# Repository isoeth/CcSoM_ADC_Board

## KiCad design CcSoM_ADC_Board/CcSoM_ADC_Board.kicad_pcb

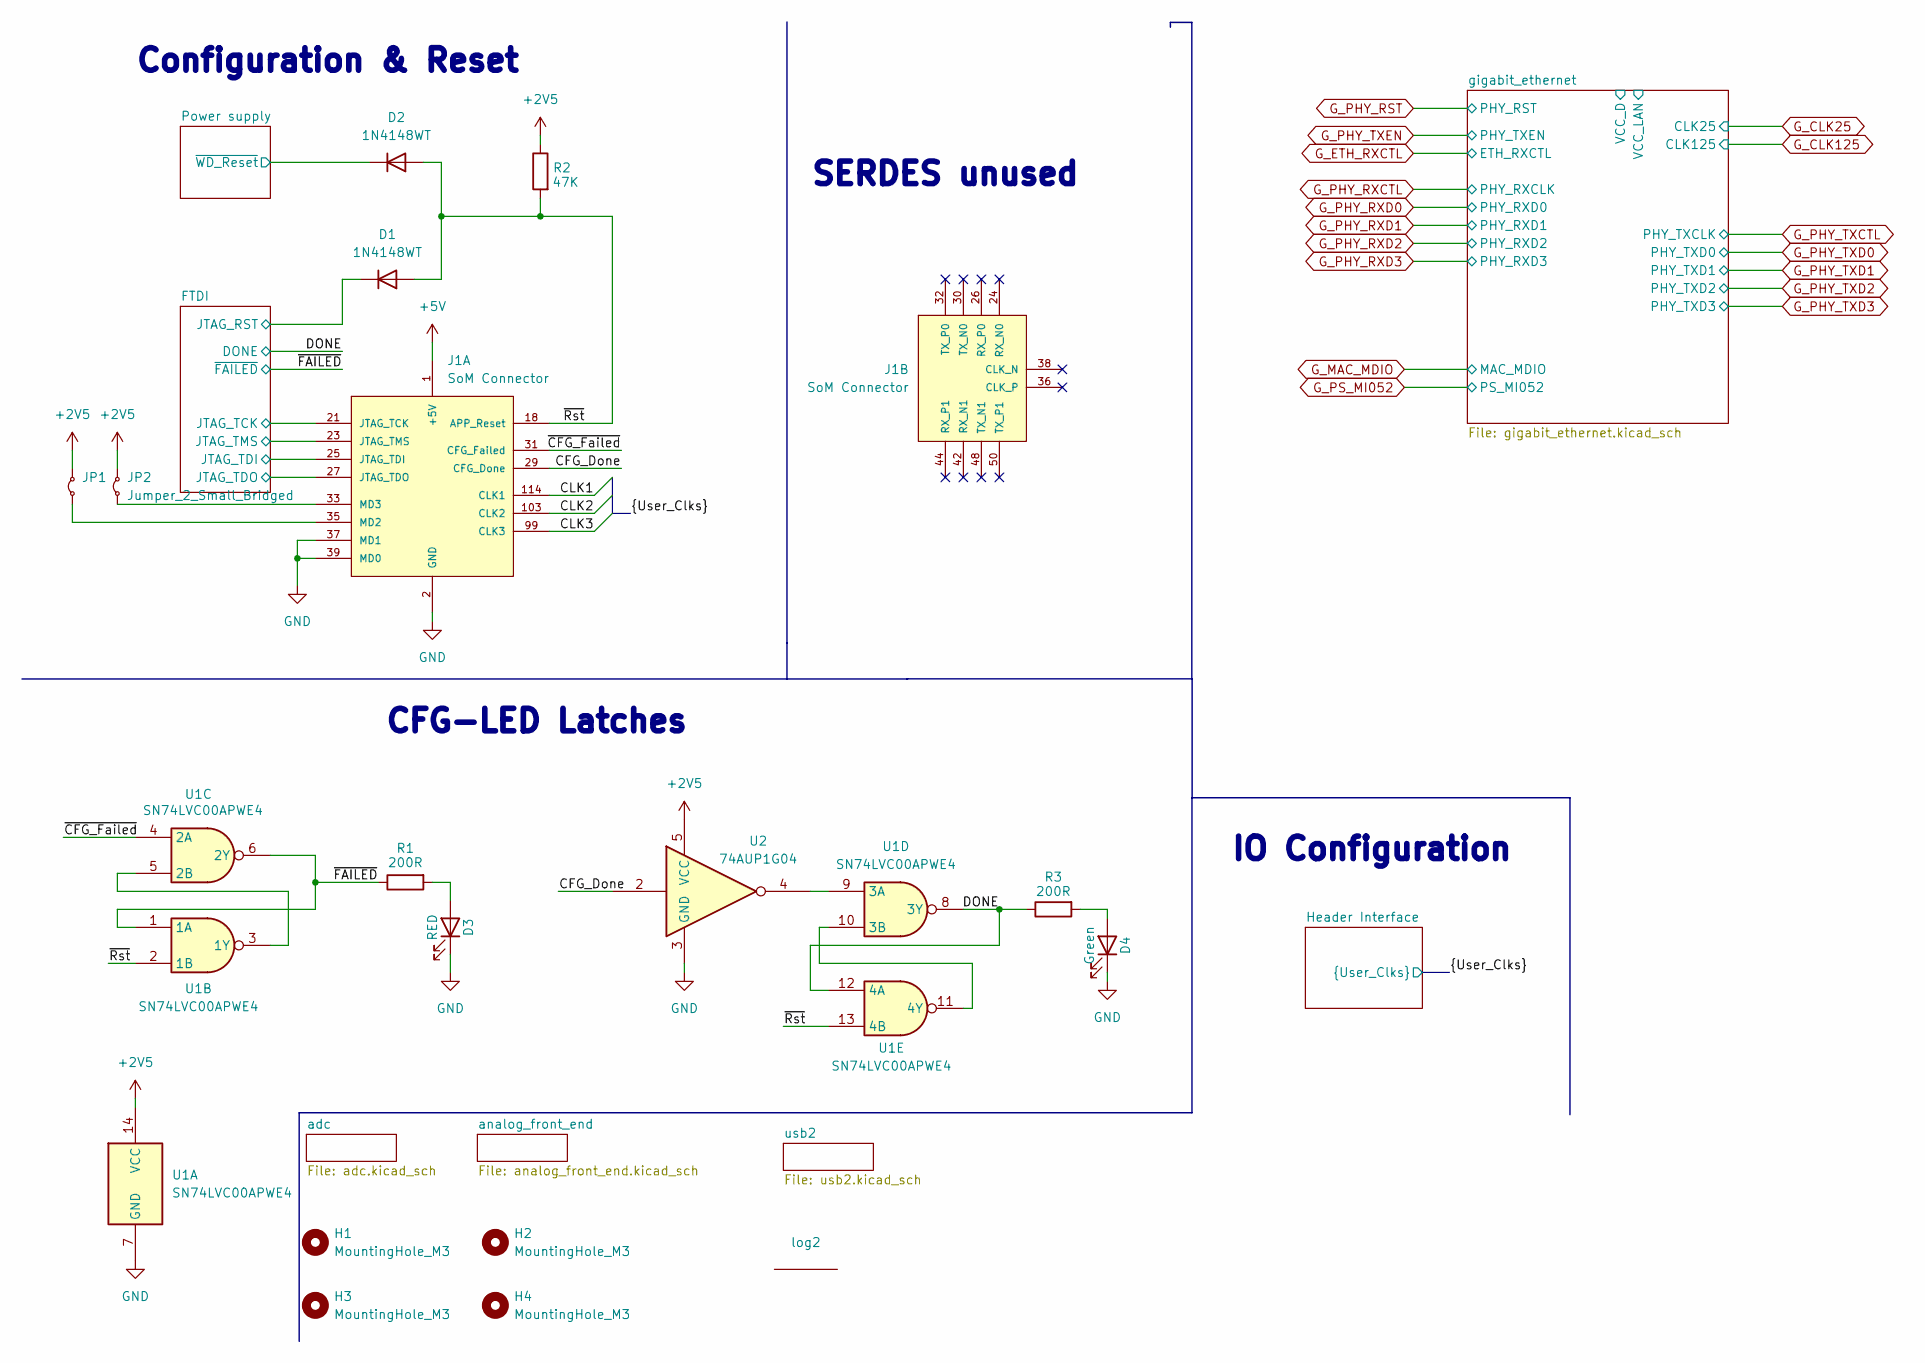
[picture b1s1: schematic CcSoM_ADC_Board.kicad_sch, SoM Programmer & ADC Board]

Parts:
D1, D2: 1N4148WT; LED_0603_1608Metric; Mouser Part Number 637-1N4148WT
D3: RED; LED_0603_1608Metric; Mouser Part Number 710-150060SS75000
D4: Green; LED_0603_1608Metric; Mouser Part Number 710-150060VS75000
H1, H2, H3, H4: MountingHole_M3; MountingHole_3.2mm_M3
J1: SoM Connector; SoM_Connector; Mouser Part Number 571-1-1473005-1
JP1, JP2: Jumper_2_Small_Bridged; TestPoint_2Pads_Pitch2.54mm_Drill0.8mm; DigiKey_no 664-G800W306018EU-ND
R1, R3: 200R; R_0603_1608Metric; Mouser Part Number 71-CRCW0603200RFKEC
R2: 47K; R_0603_1608Metric; Mouser Part Number 71-CRCW060347K0FKED
U1: SN74LVC00APWE4; TSSOP-14_4.4x5mm_P0.65mm; Mouser Part Number 595-SN74LVC00APWE4
U2: 74AUP1G04; SOT-23-5; Mouser Part Number 595-SN74AUP1G04DBVR
log2: OpenHardwareLogo

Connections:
+5V: J1.1 (+5V), J1.4 (+5V); also elsewhere on the board
/CFG_Done: J1.29 (CFG_Done), U2.2
/CLK1: J1.114 (CLK1)
/CLK2: J1.103 (CLK2)
/CLK3: J1.99 (CLK3)
/DONE: R3.1, U1.8 (3Y), U1.12 (4A); also elsewhere on the board
/FTDI/JTAG_RST: D1.1 (K); also elsewhere on the board
/FTDI/JTAG_TCK: J1.21 (JTAG_TCK); also elsewhere on the board
/FTDI/JTAG_TDI: J1.25 (JTAG_TDI); also elsewhere on the board
/FTDI/JTAG_TDO: J1.27 (JTAG_TDO); also elsewhere on the board
/FTDI/JTAG_TMS: J1.23 (JTAG_TMS); also elsewhere on the board
/Power supply/~WD_Reset: D2.1 (K); also elsewhere on the board
/~CFG_Failed: J1.31 (CFG_Failed), U1.4 (2A)
/~FAILED: R1.1, U1.1 (1A), U1.6 (2Y); also elsewhere on the board
/~Rst: D1.2 (A), D2.2 (A), J1.18 (APP_Reset), R2.2, U1.2 (1B), U1.13 (4B)
unnamed: D3.2 (A), R1.2
unnamed: D4.2 (A), R3.2
unnamed: J1.35 (MD2), JP1.2 (B)
unnamed: J1.33 (MD3), JP2.2 (B)
unnamed: U1.3 (1Y), U1.5 (2B)
unnamed: U1.9 (3A), U2.4
unnamed: U1.10 (3B), U1.11 (4Y)
OGND: D3.1 (K), D4.1 (K), J1.2 (GND), J1.3 (GND), J1.6 (GND), J1.7 (GND), J1.10 (GND), J1.11 (GND), J1.14 (GND), J1.15 (GND), J1.19 (GND), J1.20 (GND), J1.22 (GND), J1.28 (GND), J1.34 (GND), J1.37 (MD1), J1.39 (MD0), J1.40 (GND), J1.46 (GND), J1.52 (GND), J1.54 (GND), J1.97 (GND), J1.101 (GND), J1.105 (GND), J1.112 (GND), J1.116 (GND), J1.122 (GND), J1.144 (GND), J1.159 (GND), J1.162 (GND), J1.180 (GND), J1.181 (GND), J1.199 (GND), J1.S1 (SHIELD), J1.S2 (SHIELD__1), U1.7 (GND), U2.3 (GND); also elsewhere on the board
OVDD: JP1.1 (A), JP2.1 (A), R2.1, U1.14 (VCC), U2.5 (VCC); also elsewhere on the board

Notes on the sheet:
Configuration & Reset
CFG-LED Latches
IO Configuration
SERDES unused

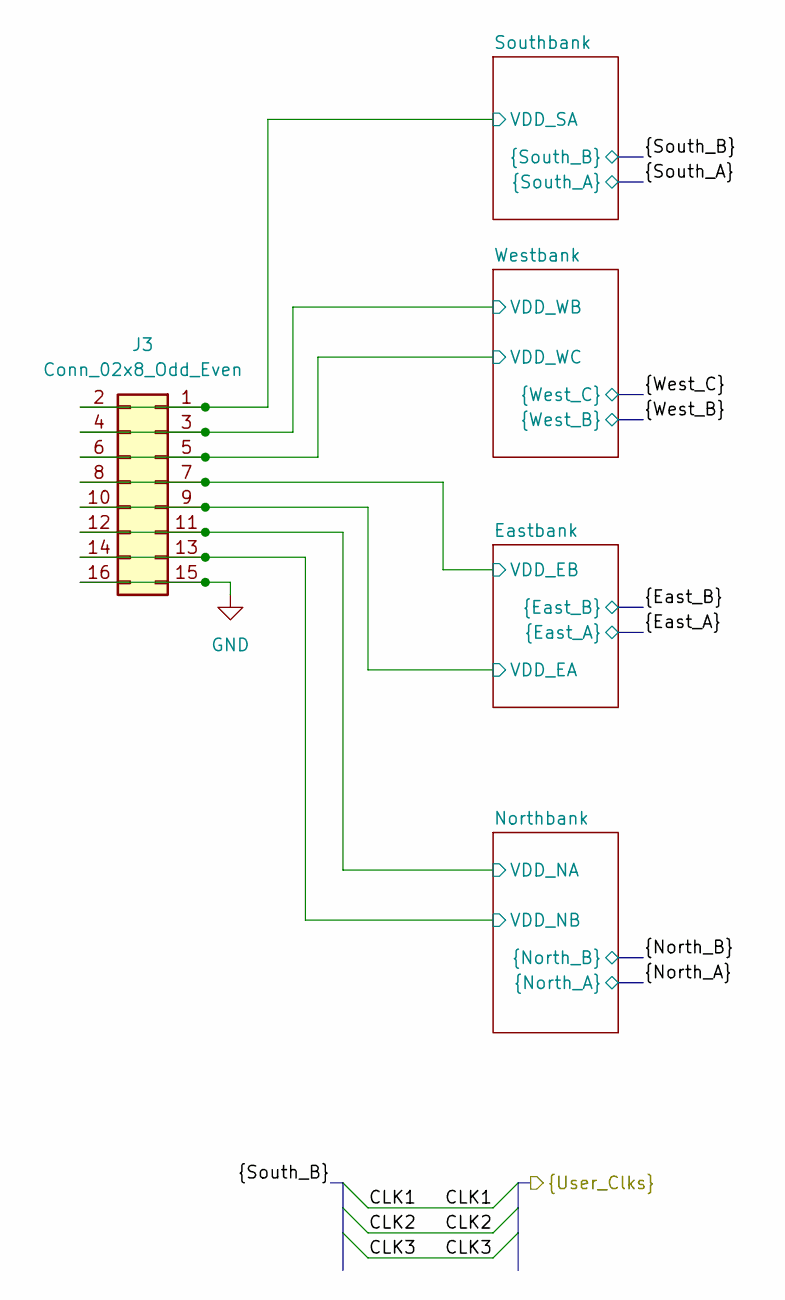
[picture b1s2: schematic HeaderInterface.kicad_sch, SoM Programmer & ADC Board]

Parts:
J3: Conn_02x8_Odd_Even; PinHeader_2x08_P2.54mm_Vertical; Mouser Part Number 649-1012938191601BLF

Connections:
/Header Interface/Eastbank/VDD_EA: J3.9, J3.10; also elsewhere on the board
/Header Interface/Eastbank/VDD_EB: J3.7, J3.8; also elsewhere on the board
/Header Interface/Northbank/VDD_NA: J3.11, J3.12; also elsewhere on the board
/Header Interface/Northbank/VDD_NB: J3.13, J3.14; also elsewhere on the board
/Header Interface/Southbank/VDD_SA: J3.1, J3.2; also elsewhere on the board
/Header Interface/Westbank/VDD_WB: J3.3, J3.4; also elsewhere on the board
/Header Interface/Westbank/VDD_WC: J3.5, J3.6; also elsewhere on the board
OGND: J3.15, J3.16; also elsewhere on the board

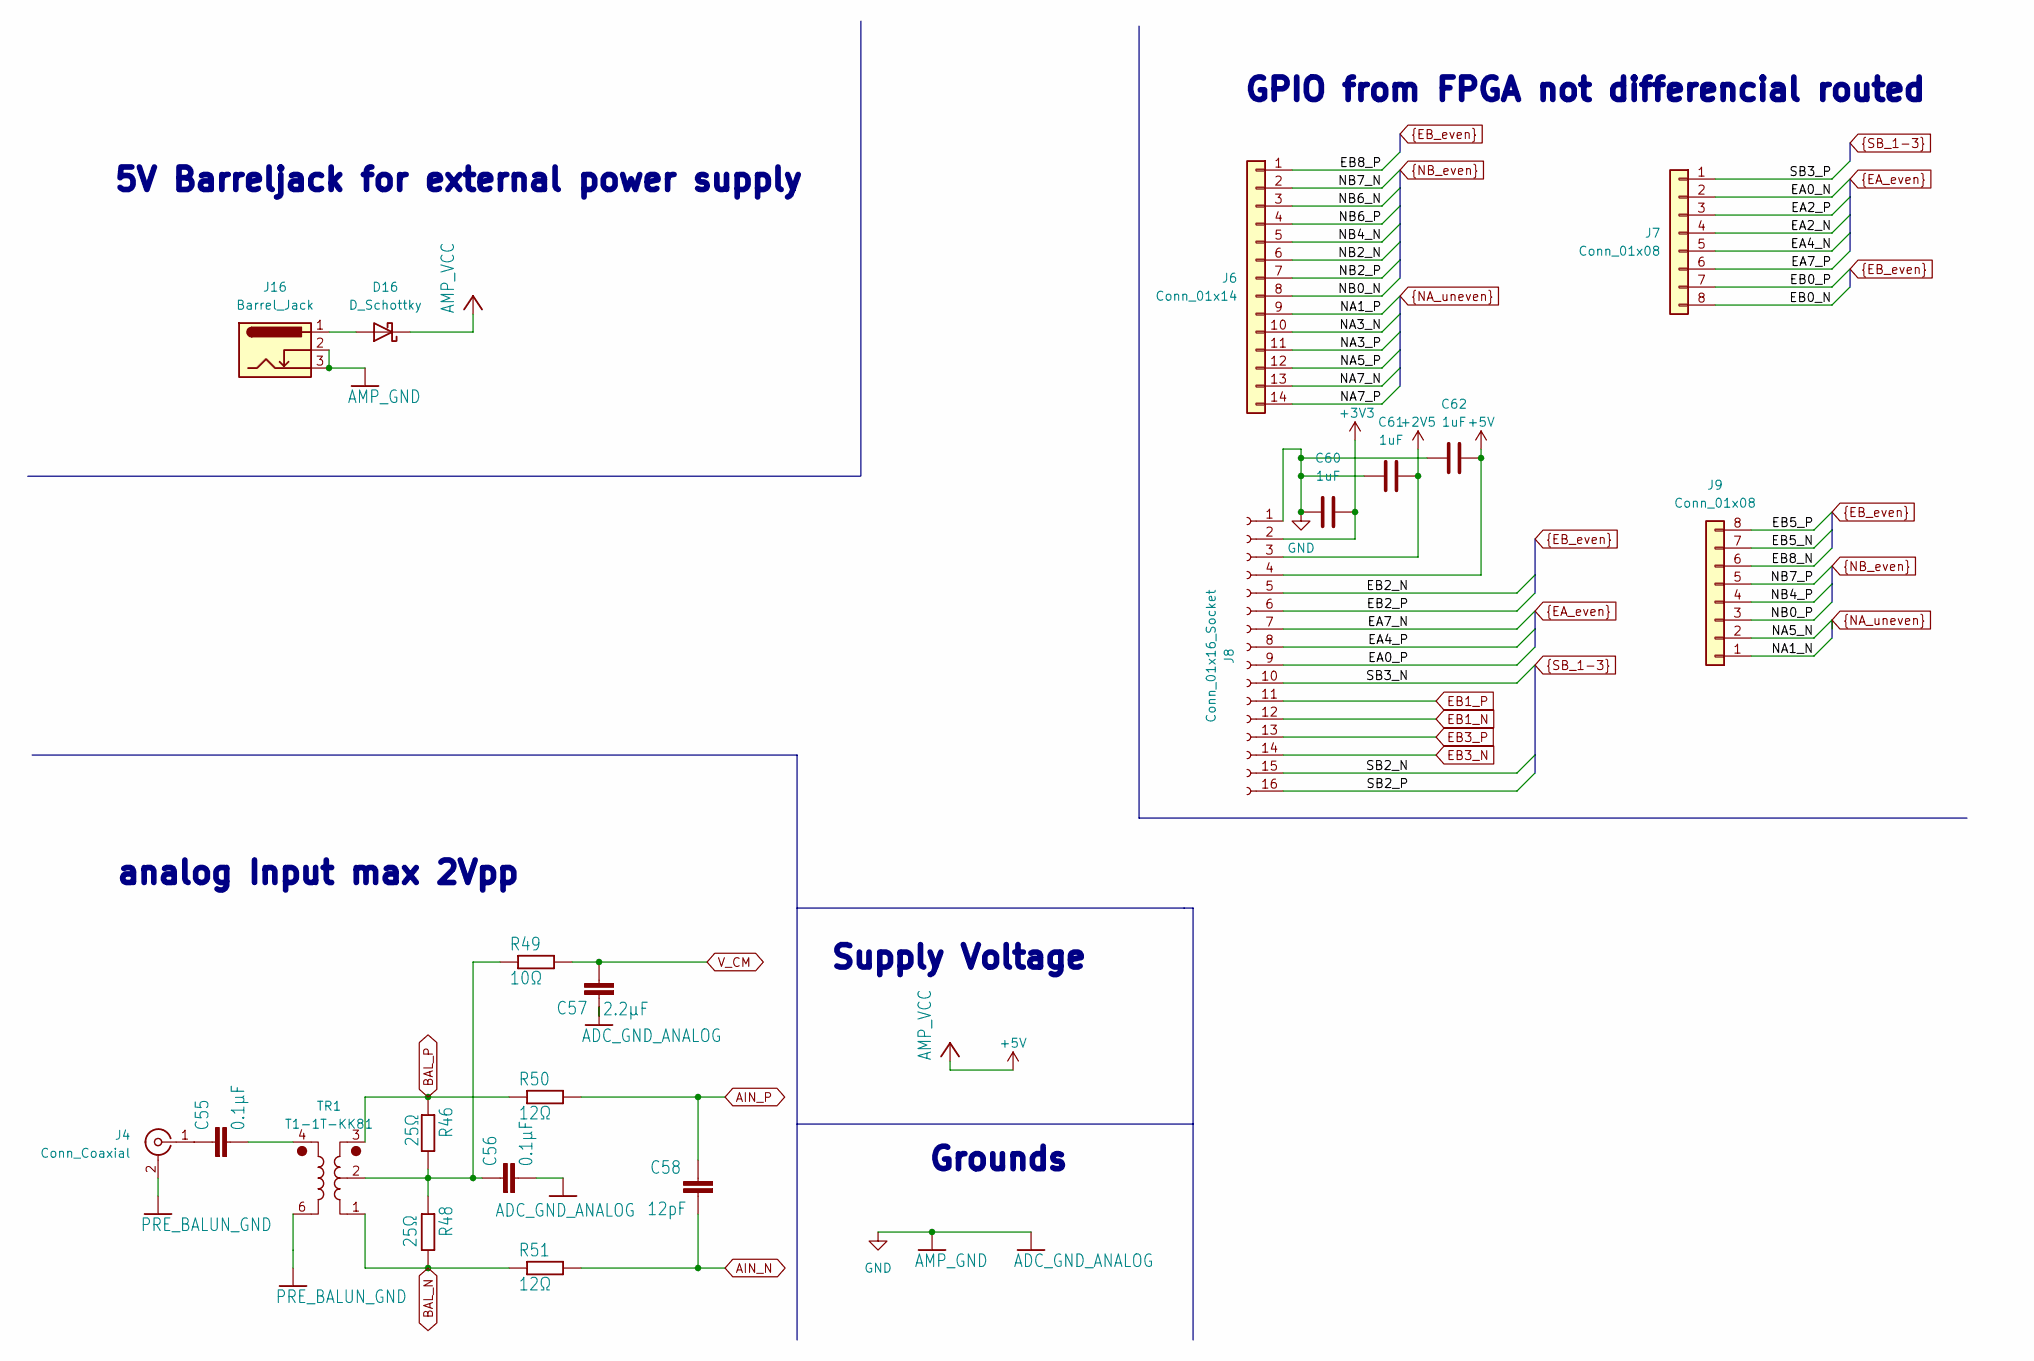
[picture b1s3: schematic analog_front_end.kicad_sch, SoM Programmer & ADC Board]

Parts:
C55, C56: 0.1μF; C_0402_1005Metric_Pad0.74x0.62mm_HandSolder; DigiKey_no C0402C104K4RACTU
C57: 2.2μF; C_0402_1005Metric_Pad0.74x0.62mm_HandSolder; DigiKey_no 490-10012-1-ND
C58: 12pF; C_0402_1005Metric_Pad0.74x0.62mm_HandSolder; DigiKey_no 399-C0402C120J5GACTUCT-ND
C60, C61, C62: 1uF; C_0603_1608Metric; Mouser Part Number 80-C0603C104M4R7411
D16: D_Schottky; D_0805_2012Metric_Pad1.15x1.40mm_HandSolder; DigiKey_no 478-7800-1-ND
J4: Conn_Coaxial; SMA_Amphenol_132134-11_Vertical; DigiKey_no ACX1995-ND
J6: Conn_01x14; PinSocket_1x14_P2.54mm_Vertical; DigiKey_no S7012-ND
J7, J9: Conn_01x08; PinSocket_1x08_P2.54mm_Vertical; DigiKey_no S7006-ND
J8: Conn_01x16_Socket; PinSocket_1x16_P2.54mm_Vertical; DigiKey_no S7014-ND
J16: Barrel_Jack; BarrelJack_CLIFF_FC681465S_SMT_Horizontal; DigiKey_no 4654-FC681465S-ND
R46, R48: 25Ω; R_0402_1005Metric_Pad0.72x0.64mm_HandSolder; DigiKey_no 478-UBR0402B250FZTR\500CT-ND
R49: 10Ω; R_0402_1005Metric_Pad0.72x0.64mm_HandSolder; DigiKey_no 541-10.0LCT-ND
R50, R51: 12Ω; R_0402_1005Metric_Pad0.72x0.64mm_HandSolder; DigiKey_no YAG2968CT-ND
TR1: T1-1T-KK81; DigiKey_no 3157-T1-1T-KK81+CT-ND

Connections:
+3V3: C60.2, J8.2; also elsewhere on the board
+5V: C62.2, D16.1 (K), J8.4; also elsewhere on the board
AIN_N: C58.1, R51.2; also elsewhere on the board
AIN_P: C58.2, R50.2; also elsewhere on the board
BAL_N: R48.2, R51.1, TR1.1
BAL_P: R46.1, R50.1, TR1.3
EA0_N: J7.2; also elsewhere on the board
EA0_P: J8.9; also elsewhere on the board
EA2_N: J7.4; also elsewhere on the board
EA2_P: J7.3; also elsewhere on the board
EA4_N: J7.5; also elsewhere on the board
EA4_P: J8.8; also elsewhere on the board
EA7_N: J8.7; also elsewhere on the board
EA7_P: J7.6; also elsewhere on the board
EB0_N: J7.8; also elsewhere on the board
EB0_P: J7.7; also elsewhere on the board
EB1_N: J8.12; also elsewhere on the board
EB1_P: J8.11; also elsewhere on the board
EB2_N: J8.5; also elsewhere on the board
EB2_P: J8.6; also elsewhere on the board
EB3_N: J8.14; also elsewhere on the board
EB3_P: J8.13; also elsewhere on the board
EB5_N: J9.7; also elsewhere on the board
EB5_P: J9.8; also elsewhere on the board
EB8_N: J9.6; also elsewhere on the board
EB8_P: J6.1; also elsewhere on the board
NA1_N: J9.1; also elsewhere on the board
NA1_P: J6.9; also elsewhere on the board
NA3_N: J6.10; also elsewhere on the board
NA3_P: J6.11; also elsewhere on the board
NA5_N: J9.2; also elsewhere on the board
NA5_P: J6.12; also elsewhere on the board
NA7_N: J6.13; also elsewhere on the board
NA7_P: J6.14; also elsewhere on the board
NB0_N: J6.8; also elsewhere on the board
NB0_P: J9.3; also elsewhere on the board
NB2_N: J6.6; also elsewhere on the board
NB2_P: J6.7; also elsewhere on the board
NB4_N: J6.5; also elsewhere on the board
NB4_P: J9.4; also elsewhere on the board
NB6_N: J6.3; also elsewhere on the board
NB6_P: J6.4; also elsewhere on the board
NB7_N: J6.2; also elsewhere on the board
NB7_P: J9.5; also elsewhere on the board
unnamed: C55.2, TR1.4
unnamed: C56.1, R46.2, R48.1, R49.1, TR1.2
unnamed: D16.2 (A), J16.1
unnamed: C55.1, J4.1 (In)
OGND: C56.2, C57.1, C60.1, C61.1, C62.1, J8.1, J16.2, J16.3; also elsewhere on the board
OVDD: C61.2, J8.3; also elsewhere on the board
PRE_BALUN_GND: J4.2 (Ext), TR1.6
SB2_N: J8.15; also elsewhere on the board
SB2_P: J8.16; also elsewhere on the board
SB3_N: J8.10; also elsewhere on the board
SB3_P: J7.1; also elsewhere on the board
V_CM: C57.2, R49.2; also elsewhere on the board

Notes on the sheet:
GPIO from FPGA not differencial routed
Supply Voltage
analog Input max 2Vpp
5V Barreljack for external power supply
Grounds

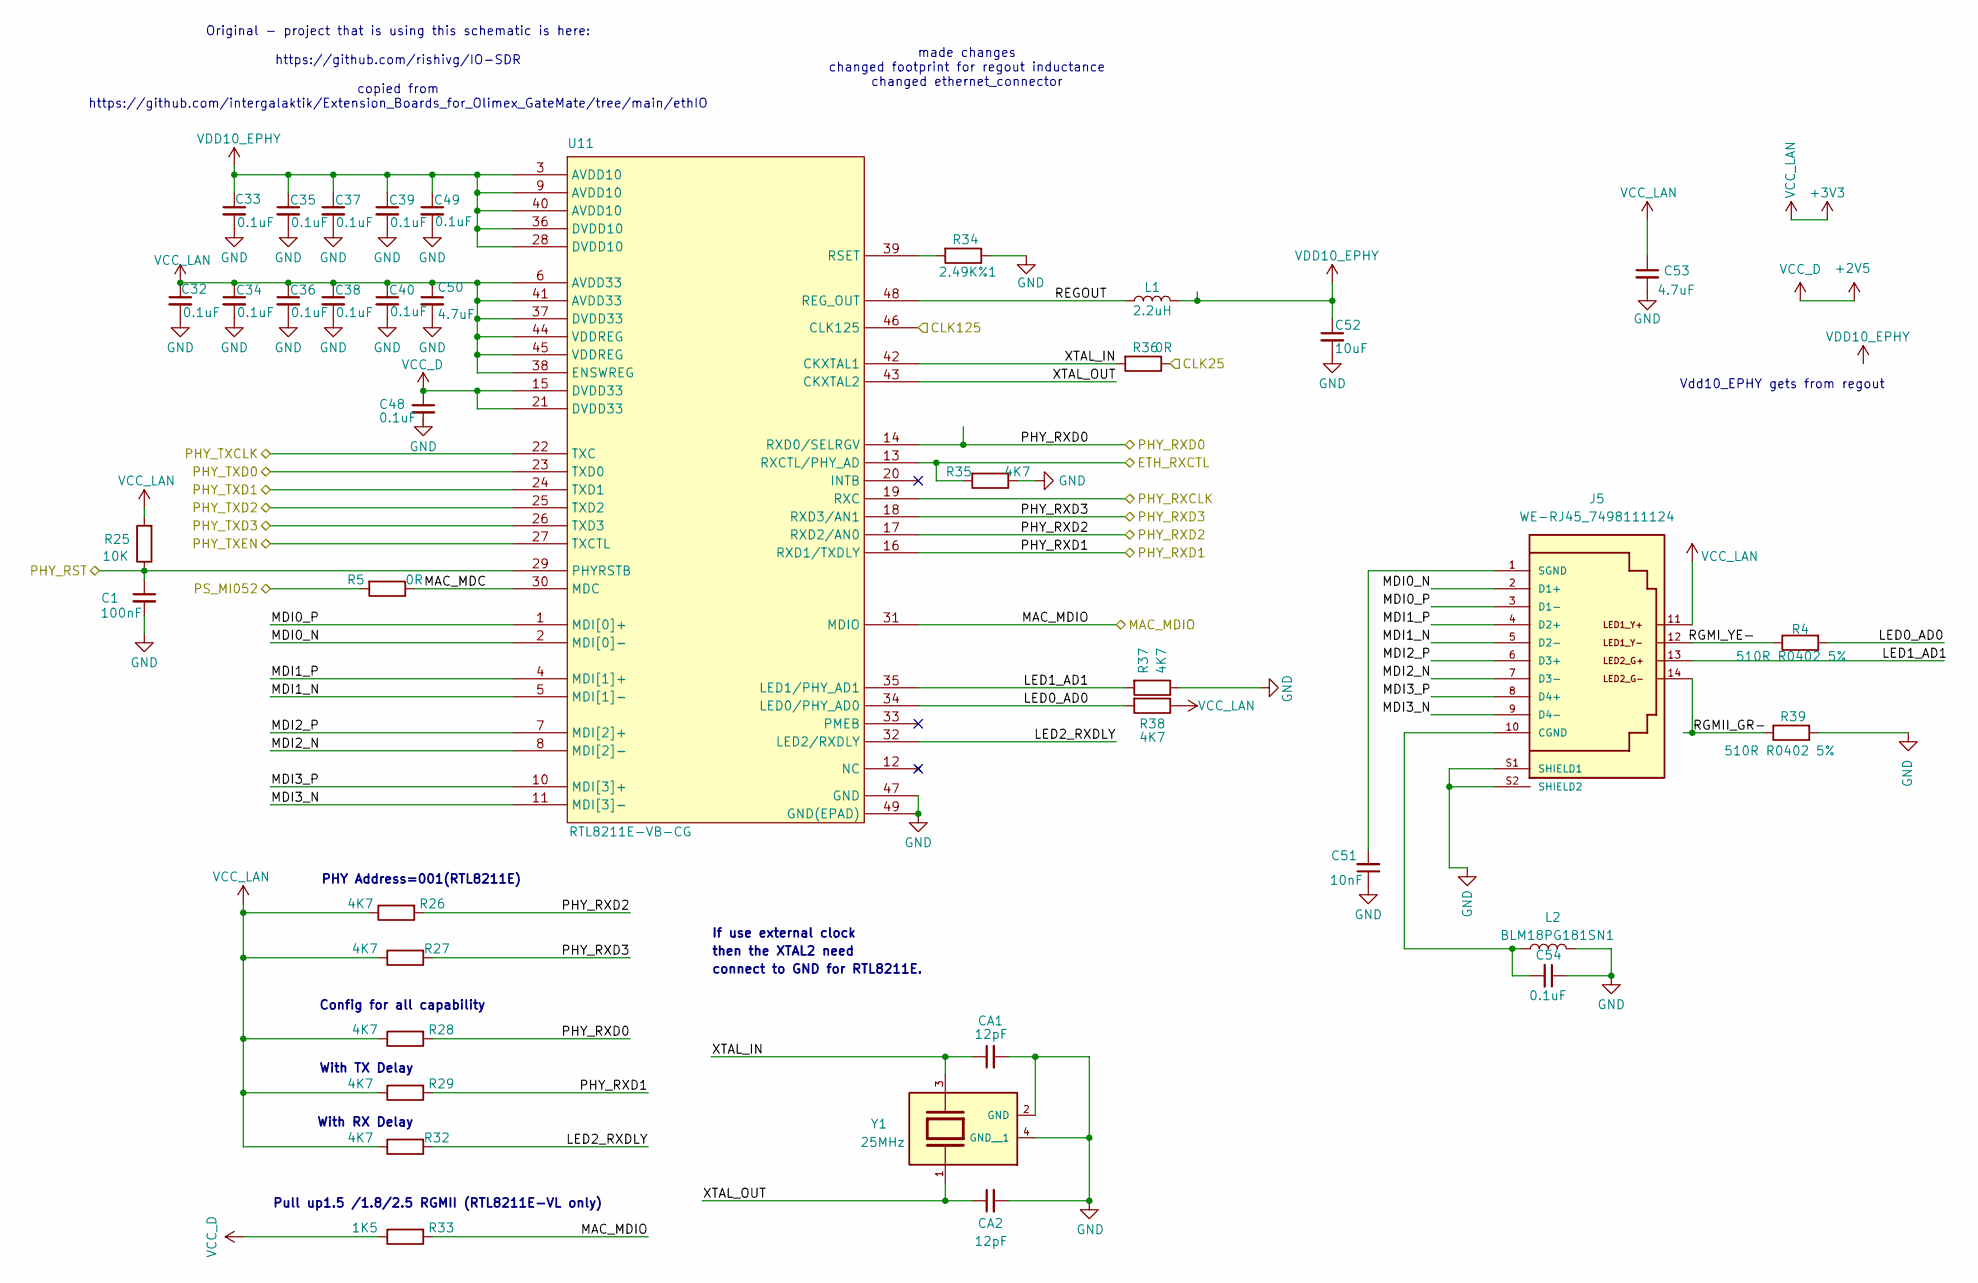
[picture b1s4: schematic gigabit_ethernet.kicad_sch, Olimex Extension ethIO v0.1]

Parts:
C1: 100nF; C_0402_1005Metric_Pad0.74x0.62mm_HandSolder; DigiKey_no 1276-CL05B104KP5VPNCCT-ND
C32, C33, C34, C35, C36, C37, C38, C39, C40, C48, C49: 0.1uF; C_0402_1005Metric_Pad0.74x0.62mm_HandSolder; DigiKey_no 399-C0402C104K4RACTUCT-ND
C50, C53: 4.7uF; C_0603_1608Metric_Pad1.08x0.95mm_HandSolder; DigiKey_no 490-7203-1-ND
C51: 10nF; C_0402_1005Metric_Pad0.74x0.62mm_HandSolder; DigiKey_no 399-C0402C103K4RACTUCT-ND
C52: 10uF; C_0805_2012Metric_Pad1.18x1.45mm_HandSolder; DigiKey_no 478-KGM21AR50J106KUCT-ND
C54: 0.1uF; C_0805_2012Metric_Pad1.18x1.45mm_HandSolder; DigiKey_no 478-KGM21NR71E104KTCT-ND
CA1, CA2: 12pF; C_0402_1005Metric_Pad0.74x0.62mm_HandSolder; DigiKey_no 399-C0402C120J5GACTUCT-ND
J5: WE-RJ45_7498111124; 7498111124; DigiKey_no 732-7498111124CT-ND
L1: 2.2uH; L_0805_2012Metric_Pad1.05x1.20mm_HandSolder; DigiKey_no 535-AOTA-B201210S2R2MTCT-ND
L2: BLM18PG181SN1; L_0603_1608Metric_Pad1.05x0.95mm_HandSolder; DigiKey_no 490-5263-1-ND
R4, R39: 510R R0402 5%; R_0402_1005Metric_Pad0.72x0.64mm_HandSolder; DigiKey_no 2019-RK73B1ETTP511JCT-ND
R5: 0R; R_0603_1608Metric_Pad0.98x0.95mm_HandSolder; DigiKey_no 311-0.0GRCT-ND
R25: 10K; R_0402_1005Metric_Pad0.72x0.64mm_HandSolder; DigiKey_no 541-10.0KLCT-ND
R26, R27, R28, R29, R32, R35, R37, R38: 4K7; R_0402_1005Metric_Pad0.72x0.64mm_HandSolder; DigiKey_no 541-4.70KLCT-ND
R33: 1K5; R_0402_1005Metric_Pad0.72x0.64mm_HandSolder; DigiKey_no 541-1.50KLCT-ND
R34: 2.49K%1; R_0402_1005Metric_Pad0.72x0.64mm_HandSolder; DigiKey_no 541-2.49KLCT-ND
R36: 0R; R_0402_1005Metric_Pad0.72x0.64mm_HandSolder; DigiKey_no 541-0.0JCT-ND
U11: RTL8211E-VB-CG; DigiKey_no 1188-SMDICRTL8211E-VB-CG-ND
Y1: 25MHz; Crystal_SMD_SeikoEpson_TSX3225-4Pin_3.2x2.5mm; PARTREV N/A; DigiKey_no SER4211CT-ND

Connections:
+3V3: C32.1, C34.1, C36.1, C38.1, C40.1, C50.1, C53.1, J5.11, R25.2, R26.1, R27.1, R28.1, R29.1, R32.1, R38.1, U11.6 (AVDD33), U11.37 (DVDD33), U11.38 (ENSWREG), U11.41 (AVDD33), U11.44 (VDDREG), U11.45 (VDDREG); also elsewhere on the board
/gigabit_ethernet/LED0_AD0: R4.2, R38.2, U11.34 (LED0/PHY_AD0)
/gigabit_ethernet/LED1_AD1: J5.13, R37.2, U11.35 (LED1/PHY_AD1)
/gigabit_ethernet/LED2_RXDLY: R32.2, U11.32 (LED2/RXDLY)
/gigabit_ethernet/MAC_MDC: R5.1, U11.30 (MDC)
/gigabit_ethernet/MDI0_N: J5.2 (D1+), U11.2 (MDI[0]-)
/gigabit_ethernet/MDI0_P: J5.3 (D1-), U11.1 (MDI[0]+)
/gigabit_ethernet/MDI1_N: J5.5 (D2-), U11.5 (MDI[1]-)
/gigabit_ethernet/MDI1_P: J5.4 (D2+), U11.4 (MDI[1]+)
/gigabit_ethernet/MDI2_N: J5.7 (D3-), U11.8 (MDI[2]-)
/gigabit_ethernet/MDI2_P: J5.6 (D3+), U11.7 (MDI[2]+)
/gigabit_ethernet/MDI3_N: J5.9 (D4-), U11.11 (MDI[3]-)
/gigabit_ethernet/MDI3_P: J5.8 (D4+), U11.10 (MDI[3]+)
/gigabit_ethernet/REGOUT: L1.1, U11.48 (REG_OUT)
/gigabit_ethernet/RGMII_GR-: J5.14, R39.1
/gigabit_ethernet/RGMI_YE-: J5.12, R4.1
/gigabit_ethernet/XTAL_IN: CA1.1, R36.2, U11.42 (CKXTAL1), Y1.3
/gigabit_ethernet/XTAL_OUT: CA2.1, U11.43 (CKXTAL2), Y1.1
G_CLK25: R36.1; also elsewhere on the board
G_CLK125: U11.46 (CLK125); also elsewhere on the board
G_ETH_RXCTL: R35.2, U11.13 (RXCTL/PHY_AD); also elsewhere on the board
G_MAC_MDIO: R33.2, U11.31 (MDIO); also elsewhere on the board
G_PHY_RST: C1.1, R25.1, U11.29 (PHYRSTB); also elsewhere on the board
G_PHY_RXCTL: U11.19 (RXC); also elsewhere on the board
G_PHY_RXD0: R28.2, U11.14 (RXD0/SELRGV); also elsewhere on the board
G_PHY_RXD1: R29.2, U11.16 (RXD1/TXDLY); also elsewhere on the board
G_PHY_RXD2: R26.2, U11.17 (RXD2/AN0); also elsewhere on the board
G_PHY_RXD3: R27.2, U11.18 (RXD3/AN1); also elsewhere on the board
G_PHY_TXCTL: U11.22 (TXC); also elsewhere on the board
G_PHY_TXD0: U11.23 (TXD0); also elsewhere on the board
G_PHY_TXD1: U11.24 (TXD1); also elsewhere on the board
G_PHY_TXD2: U11.25 (TXD2); also elsewhere on the board
G_PHY_TXD3: U11.26 (TXD3); also elsewhere on the board
G_PHY_TXEN: U11.27 (TXCTL); also elsewhere on the board
G_PS_MI052: R5.2; also elsewhere on the board
unnamed: C54.2, J5.10 (CGND), L2.2
unnamed: C51.2, J5.1 (SGND)
unnamed: R34.2, U11.39 (RSET)
OGND: C1.2, C32.2, C33.2, C34.2, C35.2, C36.2, C37.2, C38.2, C39.2, C40.2, C48.2, C49.2, C50.2, C51.1, C52.2, C53.2, C54.1, CA1.2, CA2.2, J5.S1 (SHIELD1), J5.S2 (SHIELD2), L2.1, R34.1, R35.1, R37.1, R39.2, U11.47 (GND), U11.49 (GND(EPAD)), Y1.2 (GND), Y1.4 (GND__1); also elsewhere on the board
OVDD: C48.1, R33.1, U11.15 (DVDD33), U11.21 (DVDD33); also elsewhere on the board
VDD10_EPHY: C33.1, C35.1, C37.1, C39.1, C49.1, C52.1, L1.2, U11.3 (AVDD10), U11.9 (AVDD10), U11.28 (DVDD10), U11.36 (DVDD10), U11.40 (AVDD10)

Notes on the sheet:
Original - project that is using this schematic is here: https://github.com/rishivg/IO-SDR copied from https://github.com/intergalaktik/Extension_Boards_for_Olimex_GateMate/tree/main/ethIO
Config for all capability
With TX Delay
Pull up1.5 /1.8/2.5 RGMII (RTL8211E-VL only)
Vdd10_EPHY gets from regout
then the XTAL2 need
connect to GND for RTL8211E.
made changes changed footprint for regout inductance changed ethernet_connector
If use external clock
PHY Address=001(RTL8211E)
With RX Delay

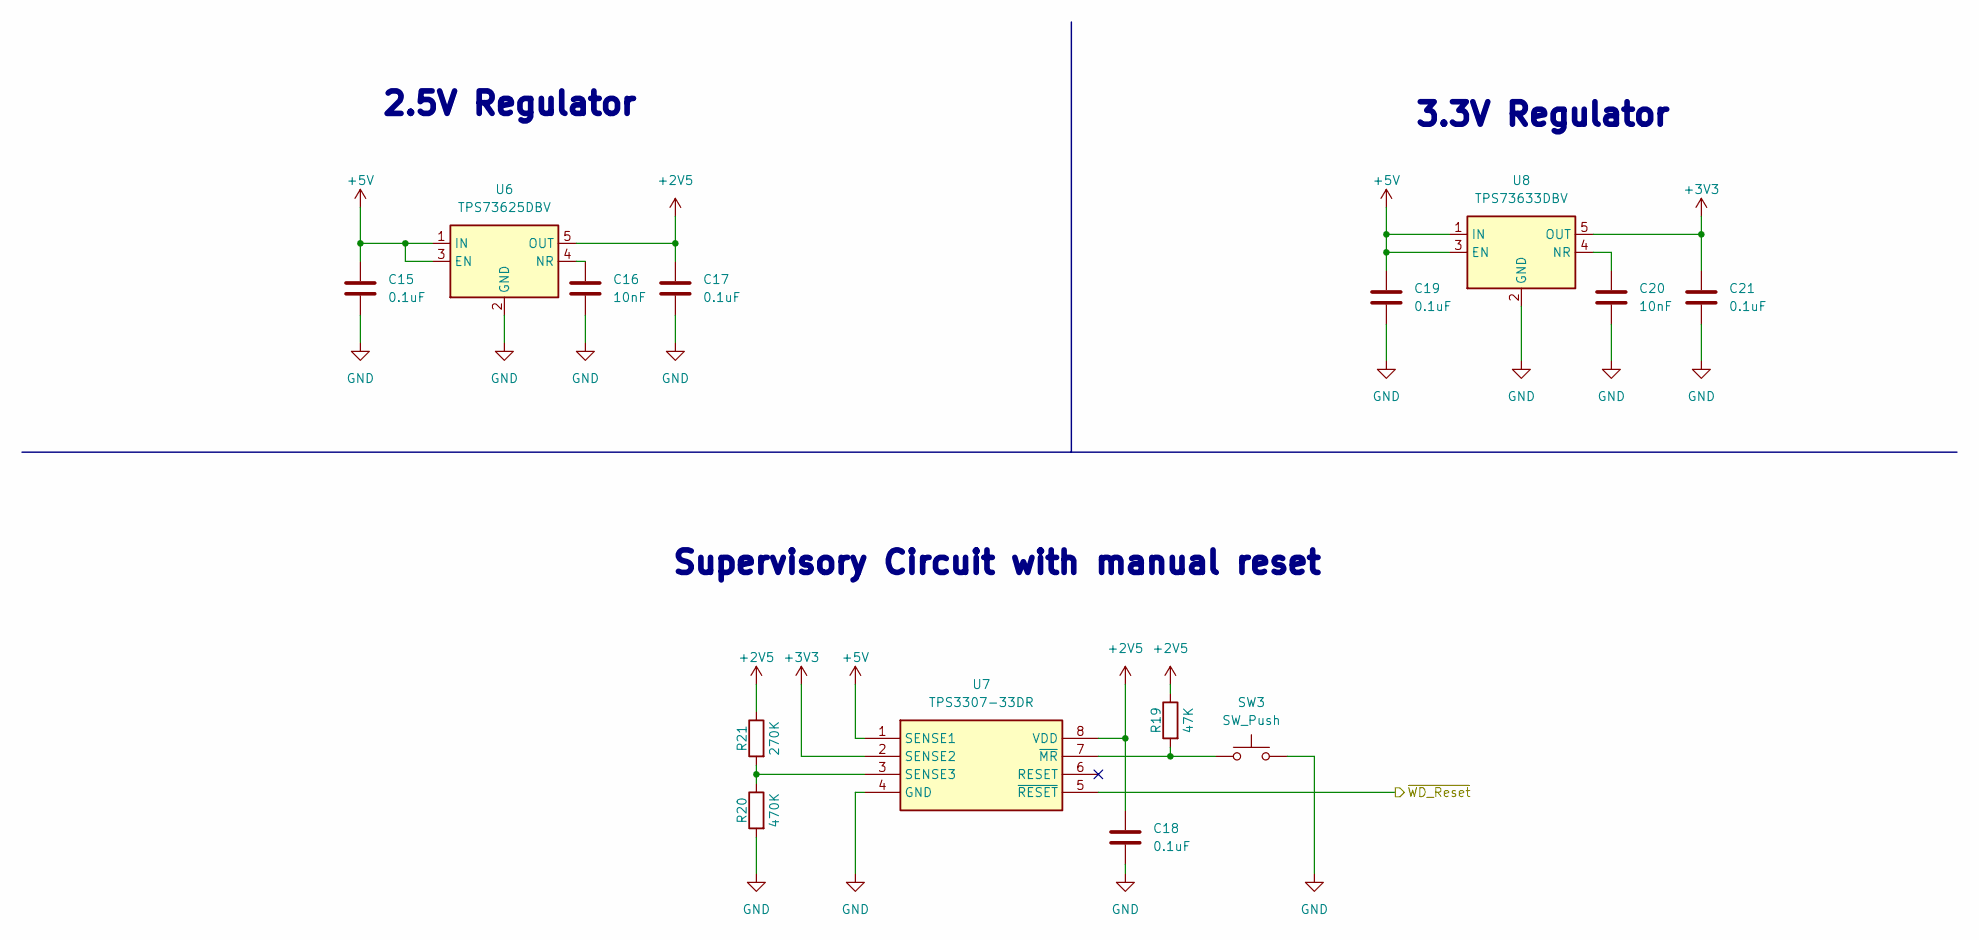
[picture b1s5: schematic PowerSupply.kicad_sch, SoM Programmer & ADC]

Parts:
C15, C17, C18, C19, C21: 0.1uF; C_0603_1608Metric; Mouser Part Number 80-C0603C104M4R7411
C16, C20: 10nF; C_0603_1608Metric; Mouser Part Number 80-C0603X103J4HAUTO
R19: 47K; R_0603_1608Metric; Mouser Part Number 71-CRCW060347K0FKED
R20: 470K; R_0603_1608Metric; Mouser Part Number 71-CRCW0603470KFKEAH
R21: 270K; R_0603_1608Metric; Mouser Part Number 71-CRCW0603-270K-E3
SW3: SW_Push; SW_SPST_TL3305A; Mouser Part Number 612-TL3305AF260QG
U6: TPS73625DBV; SOT-23-5; Mouser Part Number 595-TPS73625DBVT
U7: TPS3307-33DR; SOIC-8_5.8x3.81mm; Mouser Part Number 595-TPS3307-33DR
U8: TPS73633DBV; SOT-23-5; Mouser Part Number 595-TPS73633DBVRG4

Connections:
+3V3: C21.1, U7.2 (SENSE2), U8.5 (OUT); also elsewhere on the board
+5V: C15.1, C19.1, U6.1 (IN), U6.3 (EN), U7.1 (SENSE1), U8.1 (IN), U8.3 (EN); also elsewhere on the board
/Power supply/~WD_Reset: U7.5 (~RESET); also elsewhere on the board
unnamed: C16.1, U6.4 (NR)
unnamed: R20.1, R21.2, U7.3 (SENSE3)
unnamed: R19.2, SW3.1, U7.7 (~MR)
unnamed: C20.1, U8.4 (NR)
OGND: C15.2, C16.2, C17.2, C18.2, C19.2, C20.2, C21.2, R20.2, SW3.2, U6.2 (GND), U7.4 (GND), U8.2 (GND); also elsewhere on the board
OVDD: C17.1, C18.1, R19.1, R21.1, U6.5 (OUT), U7.8 (VDD); also elsewhere on the board

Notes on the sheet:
Supervisory Circuit with manual reset
3.3V Regulator
2.5V Regulator

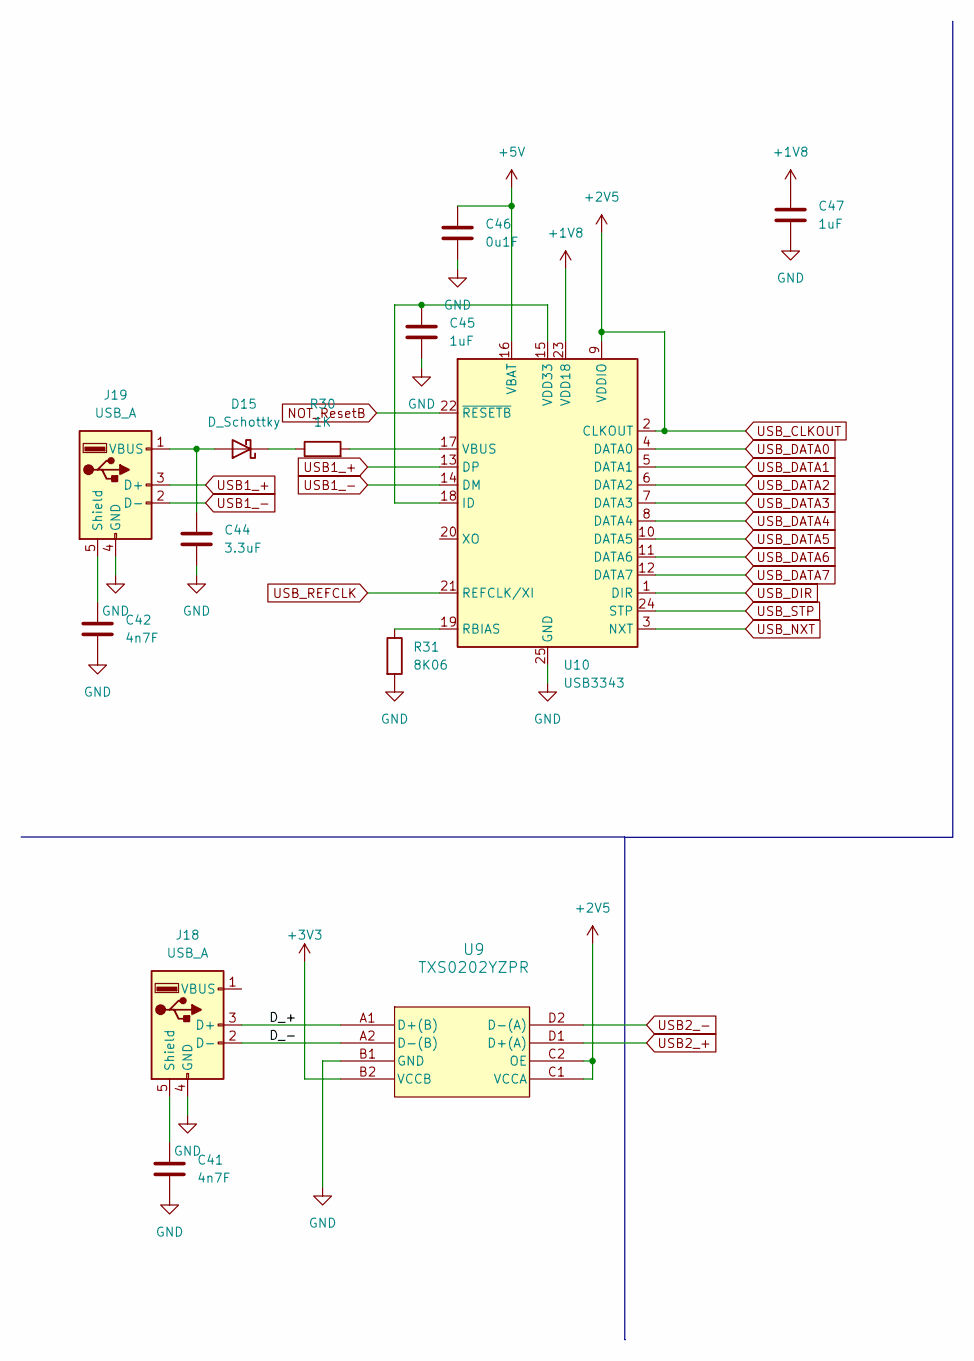
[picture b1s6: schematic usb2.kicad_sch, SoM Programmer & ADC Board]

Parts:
C41, C42: 4n7F; C_0603_1608Metric; DigiKey_no 399-C0603C472K5RACTUCT-ND
C44: 3.3uF; C_0603_1608Metric; DigiKey_no 399-3481-1-ND
C45, C47: 1uF; C_0603_1608Metric; DigiKey_no 399-C0603C105K4RACTUCT-ND
C46: 0u1F; C_0603_1608Metric; DigiKey_no 311-1088-1-ND
D15: D_Schottky; D_0805_2012Metric_Pad1.15x1.40mm_HandSolder; DigiKey_no 478-7800-1-ND
J18, J19: USB_A; USB_A_Stewart_SS-52100-001_Horizontal; DigiKey_no 380-1412-ND
R30: 1K; R_0603_1608Metric; DigiKey_no RMCF0603FT1K00CT-ND
R31: 8K06; R_0603_1608Metric; DigiKey_no 541-8.06KHCT-ND
U9: TXS0202YZPR; YZP8; Mouser Part Number 595-TXS0202YZPR; DigiKey_no 296-29072-1-ND
U10: USB3343; QFN-24-1EP_4x4mm_P0.5mm_EP2.6x2.6mm; DigiKey_no 638-1116-1-ND

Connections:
+1V8: C47.1, U10.23 (VDD18)
+3V3: U9.B2 (VCCB); also elsewhere on the board
+5V: C46.1, U10.16 (VBAT); also elsewhere on the board
/usb2/D_+: J18.3 (D+), U9.A1 (D+(B))
/usb2/D_-: J18.2 (D-), U9.A2 (D-(B))
NOT_ResetB: U10.22 (~RESETB); also elsewhere on the board
unnamed: C44.1, D15.2 (A), J19.1 (VBUS)
unnamed: D15.1 (K), R30.1
unnamed: C41.1, J18.5 (Shield)
unnamed: C42.1, J19.5 (Shield)
unnamed: C45.1, U10.15 (VDD33), U10.18 (ID)
unnamed: R31.1, U10.19 (RBIAS)
unnamed: R30.2, U10.17 (VBUS)
OGND: C41.2, C42.2, C44.2, C45.2, C46.2, C47.2, J18.4 (GND), J19.4 (GND), R31.2, U9.B1 (GND), U10.25 (GND); also elsewhere on the board
OVDD: U9.C1 (VCCA), U9.C2 (OE), U10.2 (CLKOUT), U10.9 (VDDIO); also elsewhere on the board
USB1_+: J19.3 (D+), U10.13 (DP)
USB1_-: J19.2 (D-), U10.14 (DM)
USB2_+: U9.D1 (D+(A)); also elsewhere on the board
USB2_-: U9.D2 (D-(A)); also elsewhere on the board
USB_DATA0: U10.4 (DATA0); also elsewhere on the board
USB_DATA1: U10.5 (DATA1); also elsewhere on the board
USB_DATA2: U10.6 (DATA2); also elsewhere on the board
USB_DATA3: U10.7 (DATA3); also elsewhere on the board
USB_DATA4: U10.8 (DATA4); also elsewhere on the board
USB_DATA5: U10.10 (DATA5); also elsewhere on the board
USB_DATA6: U10.11 (DATA6); also elsewhere on the board
USB_DATA7: U10.12 (DATA7); also elsewhere on the board
USB_DIR: U10.1 (DIR); also elsewhere on the board
USB_NXT: U10.3 (NXT); also elsewhere on the board
USB_REFCLK: U10.21 (REFCLK/XI); also elsewhere on the board
USB_STP: U10.24 (STP); also elsewhere on the board

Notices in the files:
CcSoM_ADC_Board/gigabit_ethernet.kicad_sch:
GPL-3.0
